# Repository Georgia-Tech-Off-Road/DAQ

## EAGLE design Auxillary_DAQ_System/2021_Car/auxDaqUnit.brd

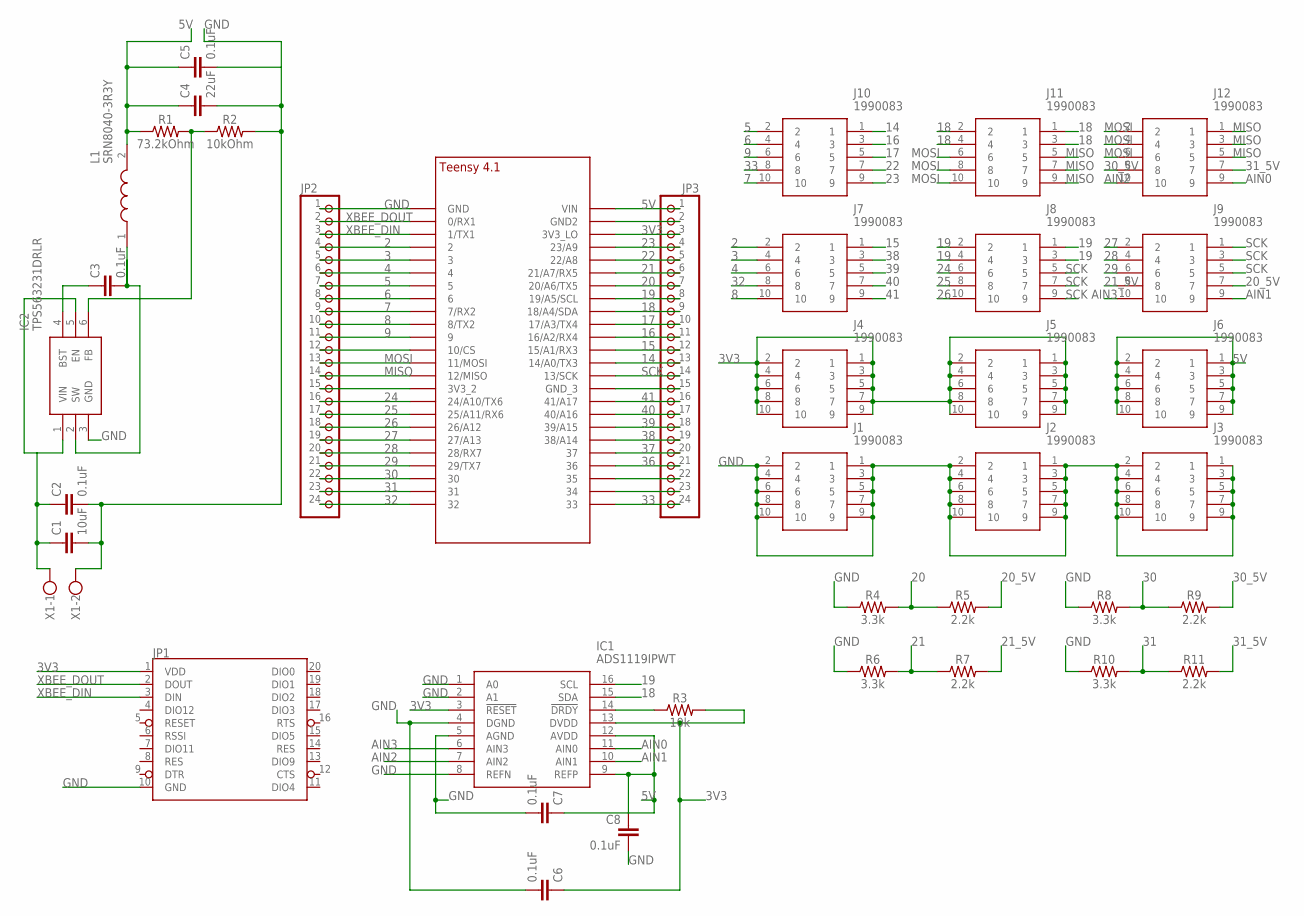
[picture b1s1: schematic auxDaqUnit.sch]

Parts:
C1: 10uF; 0603
C2, C3, C5, C6, C7, C8: 0.1uF; 0603
C4: 22uF; 0805
IC1: ADS1119IPWT; SOP65P640X120-16N
IC2: TPS563231DRLR; SOTFL50P160X60-6N
J1, J2, J3, J4, J5, J6, J7, J8, J9, J10, J11, J12: 1990083
JP1: XBEE
JP2, JP3: PINHD-1X24; 1X24
L1: SRN8040-3R3Y
R1: 73.2kOhm; 0603
R2: 10kOhm; 0603
R3: 10k; 0603
R4, R6, R8, R10: 3.3k; 0603
R5, R7, R9, R11: 2.2k; 0603
U$1: TEENSY_4.1_SIMPLE
X1: W237-102

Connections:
2: J7.2, JP2.4, U$1.2
3: J7.4, JP2.5, U$1.3/CANTX (3)
3V3: C6.1, IC1.3 (!RESET), IC1.13 (DVDD), J4.1, J4.2, J4.3, J4.4, J4.5, J4.6, J4.7, J4.8, J4.9, J4.10, J5.1, J5.2, J5.3, J5.4, J5.5, J5.6, J5.7, J5.8, J5.9, J5.10, JP1.1 (VDD), JP3.3, R3.2, U$1.3V3_LO
4: J7.6, JP2.6, U$1.4/CANRX (4)
5: J10.2, JP2.7, U$1.5
5V: C4.1, C5.1, C7.1, C8.1, IC1.9 (REFP), IC1.12 (AVDD), J6.1, J6.2, J6.3, J6.4, J6.5, J6.6, J6.7, J6.8, J6.9, J6.10, JP3.1, L1.2, R1.1, U$1.VIN
6: J10.4, JP2.8, U$1.6
7: J10.10, JP2.9, U$1.7 (7/RX2)
8: J7.10, JP2.10, U$1.8 (8/TX2)
9: J10.6, JP2.11, U$1.9/CS (9)
14: J10.1, JP3.13, U$1.14/A0 (14/A0/TX3)
15: J7.1, JP3.12, U$1.15/A1 (15/A1/RX3)
16: J10.3, JP3.11, U$1.16/A2 (16/A2/RX4)
17: J10.5, JP3.10, U$1.17/A3 (17/A3/TX4)
18: IC1.15 (SDA), J11.1, J11.2, J11.3, J11.4, JP3.9, U$1.18/A4/SDA
19: IC1.16 (SCL), J8.1, J8.2, J8.3, J8.4, JP3.8, U$1.19/A5/SCL
20: JP3.7, R4.2, R5.1, U$1.20/A6 (20/A6/TX5)
20_5V: J9.7, R5.2
21: JP3.6, R6.2, R7.1, U$1.21/A7 (21/A7/RX5)
21_5V: J9.8, R7.2
22: J10.7, JP3.5, U$1.22/A8
23: J10.9, JP3.4, U$1.23/A9
24: J8.6, JP2.16, U$1.24/A10 (24/A10/TX6)
25: J8.8, JP2.17, U$1.25/A11 (25/A11/RX6)
26: J8.10, JP2.18, U$1.26/A12
27: J9.2, JP2.19, U$1.27/A13
28: J9.4, JP2.20, U$1.28 (28/RX7)
29: J9.6, JP2.21, U$1.29 (29/TX7)
30: JP2.22, R8.2, R9.1, U$1.30
30_5V: J12.8, R9.2
31: JP2.23, R10.2, R11.1, U$1.31
31_5V: J12.7, R11.2
32: J7.8, JP2.24, U$1.32
33: J10.8, JP3.24, U$1.33
36: JP3.21, U$1.36
37: JP3.20, U$1.37
38: J7.3, JP3.19, U$1.38/A14
39: J7.5, JP3.18, U$1.39/A15
40: J7.7, JP3.17, U$1.40/A16
41: J7.9, JP3.16, U$1.41/A17
AIN0: IC1.11 (AIN0), J12.9
AIN1: IC1.10 (AIN1), J9.9
AIN2: IC1.7 (AIN2), J12.10
AIN3: IC1.6 (AIN3), J9.10
GND: C1.2, C2.2, C4.2, C5.2, C6.2, C7.2, C8.2, IC1.1 (A0), IC1.2 (A1), IC1.4 (DGND), IC1.5 (AGND), IC1.8 (REFN), IC2.3 (GND), J1.1, J1.2, J1.3, J1.4, J1.5, J1.6, J1.7, J1.8, J1.9, J1.10, J2.1, J2.2, J2.3, J2.4, J2.5, J2.6, J2.7, J2.8, J2.9, J2.10, J3.1, J3.2, J3.3, J3.4, J3.5, J3.6, J3.7, J3.8, J3.9, J3.10, JP1.10 (GND), JP2.1, R2.2, R4.1, R6.1, R8.1, R10.1, U$1.GND, X1.2
GNDBLOCK: JP3.2, U$1.GND2
MISO: J11.5, J11.7, J11.9, J12.1, J12.3, J12.5, JP2.14, U$1.12/MISO
MOSI: J11.6, J11.8, J11.10, J12.2, J12.4, J12.6, JP2.13, U$1.11/MOSI
unnamed: C3.1, IC2.4 (BST)
unnamed: C1.1, C2.1, IC2.1 (VIN), IC2.5 (EN), X1.1
unnamed: C3.2, IC2.2 (SW), L1.1
unnamed: IC1.14 (!DRDY), R3.1
unnamed: IC2.6 (FB), R1.2, R2.1
unnamed: JP2.12, U$1.10/CS
unnamed: JP2.15, U$1.3V3_2
unnamed: JP3.15, U$1.GND3 (GND_3)
unnamed: JP3.22, U$1.35
unnamed: JP3.23, U$1.34
SCK: J8.5, J8.7, J8.9, J9.1, J9.3, J9.5, JP3.14, U$1.13/SCK
XBEE_DIN: JP1.3 (DIN), JP2.3, U$1.1/TX (1/TX1)
XBEE_DOUT: JP1.2 (DOUT), JP2.2, U$1.0/RX (0/RX1)

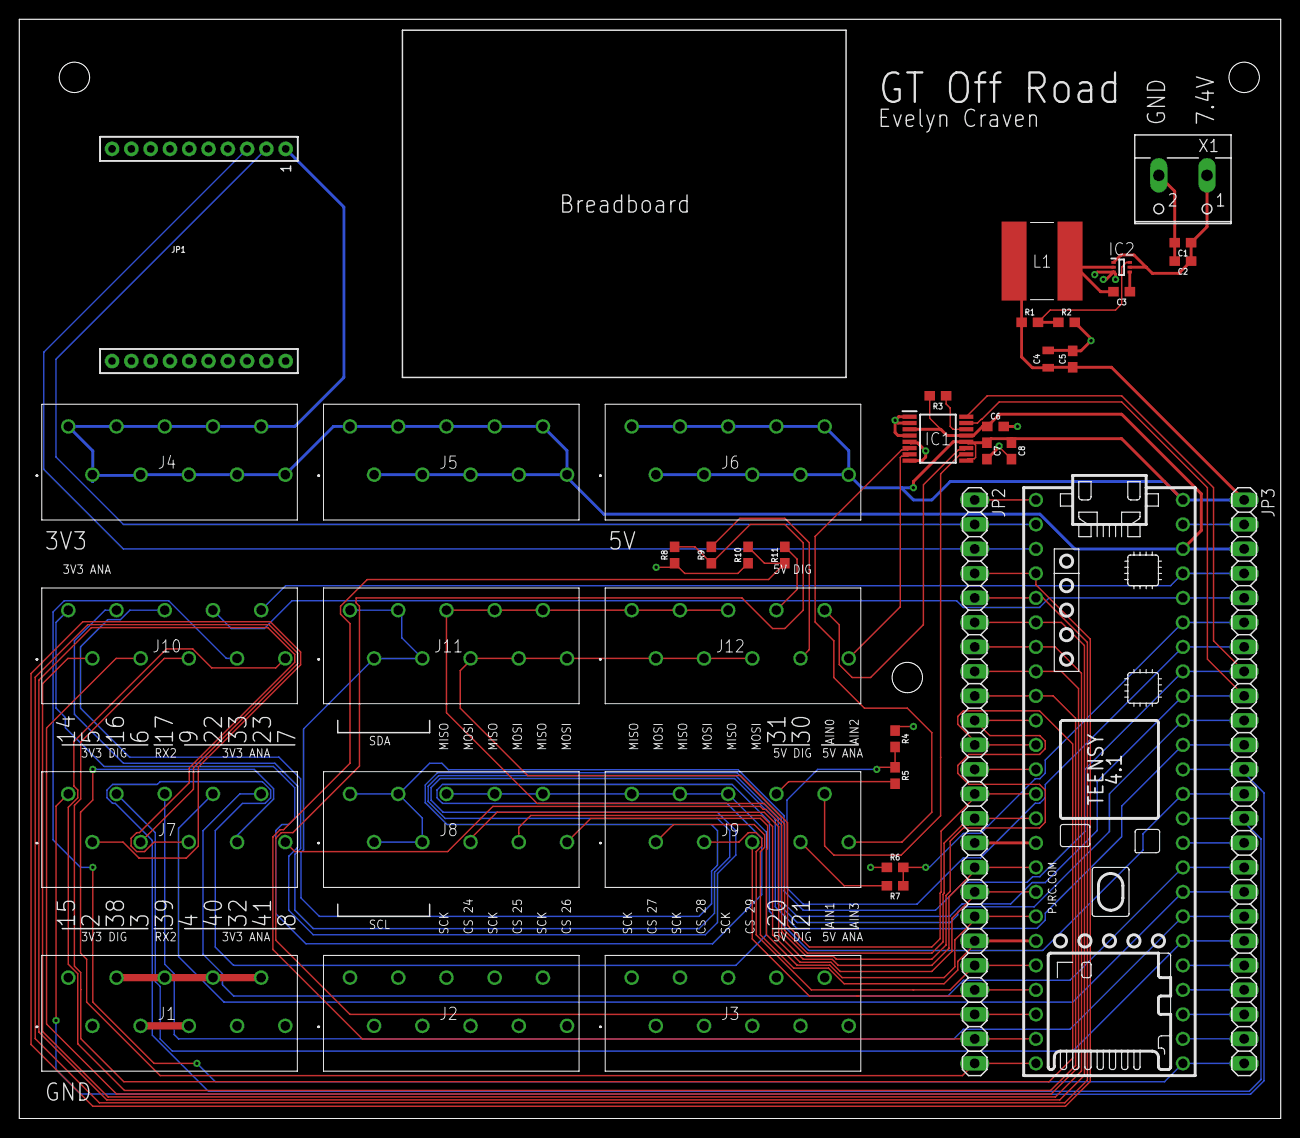
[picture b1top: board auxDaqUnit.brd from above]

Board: 2 copper layers, 130.8 x 114.0 mm, 39 parts (0 on the bottom side), 61 nets.

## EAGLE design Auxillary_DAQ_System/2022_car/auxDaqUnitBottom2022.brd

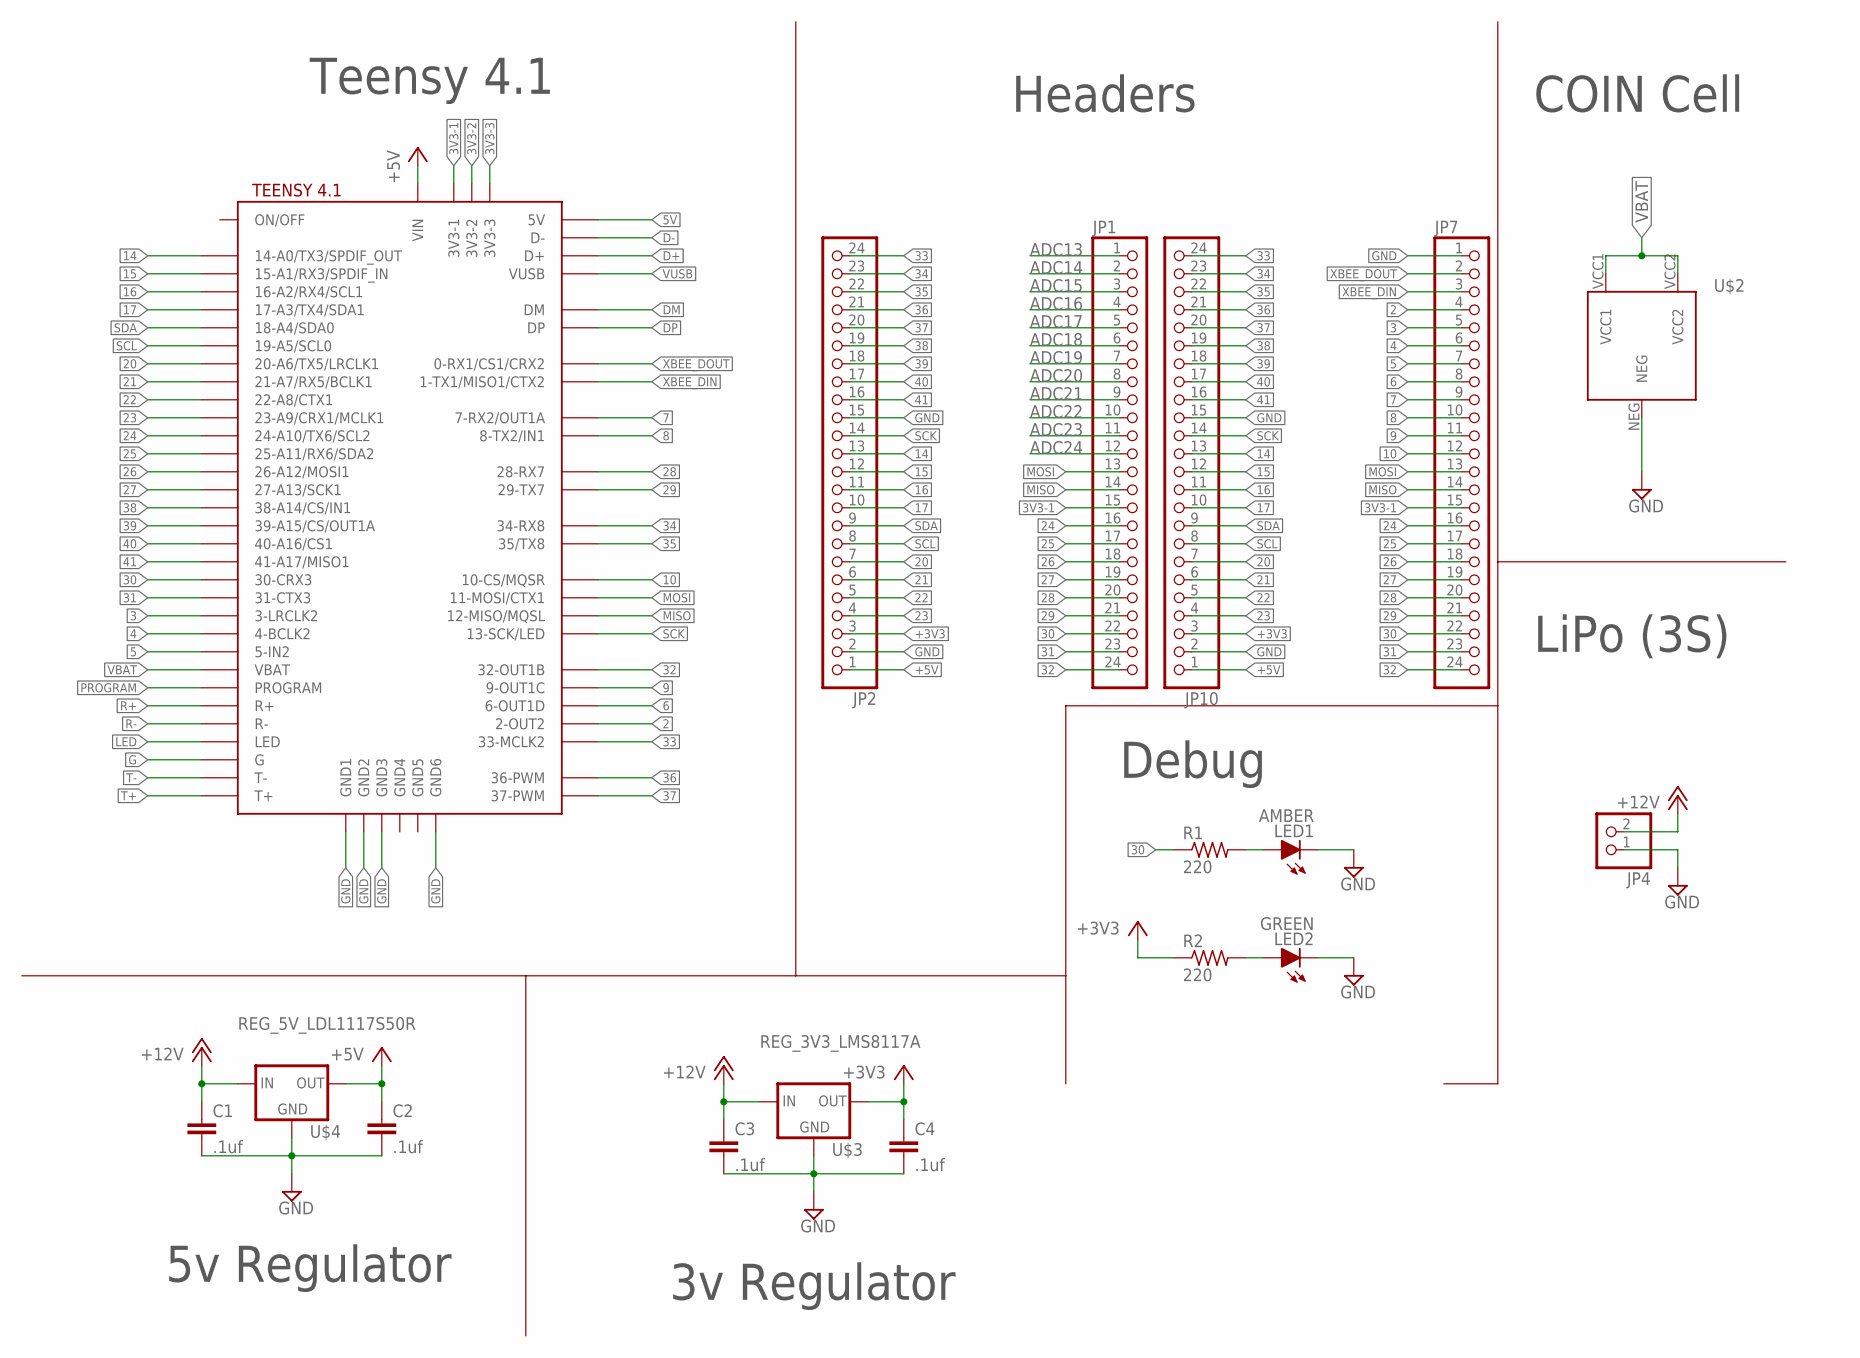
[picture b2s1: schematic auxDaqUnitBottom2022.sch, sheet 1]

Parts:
C1, C2, C3, C4: .1uf; C0603
JP1, JP2, JP7, JP10: PINHD-1X24; 1X24
JP4: PINHD-1X2; 1X02
LED1: AMBER; LED-603
LED2: GREEN; LED-603
R1, R2: 220; R0603
U$1: TEENSY41
U$2: KEYSTONE3035
U$3: REG_3V3_LMS8117A; SOT223
U$4: REG_5V_LDL1117S50R; SOT230P700X180-4N

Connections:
2: JP7.4, U$1.2-OUT2; also elsewhere on the board
3: JP7.5, U$1.3-LRCLK2; also elsewhere on the board
3V3-1: JP1.15, JP7.15, U$1.3V3-1
3V3-2: U$1.3V3-2
3V3-3: U$1.3V3-3
4: JP7.6, U$1.4-BCLK2; also elsewhere on the board
5: JP7.7, U$1.5-IN2; also elsewhere on the board
5V: U$1.+5V (5V)
6: JP7.8, U$1.6-OUT1D; also elsewhere on the board
7: JP7.9, U$1.7-RX2/OUT1A; also elsewhere on the board
8: JP7.10, U$1.8-TX2/IN2 (8-TX2/IN1); also elsewhere on the board
9: JP7.11, U$1.9-OUT1C; also elsewhere on the board
10: JP7.12, U$1.10-CS\MQSR (10-CS/MQSR); also elsewhere on the board
14: JP2.13, JP10.13, U$1.14-A0/TX3/SPDIF_OUT; also elsewhere on the board
15: JP2.12, JP10.12, U$1.15-A1/RX3/SPDIF_IN
16: JP2.11, JP10.11, U$1.16-A2/RX4/SCL1
17: JP2.10, JP10.10, U$1.17-A3/TX4/SDA1
20: JP2.7, JP10.7, U$1.20-A6/TX5/LRCLK1
21: JP2.6, JP10.6, U$1.21-A7/RX5/BCLK1
22: JP2.5, JP10.5, U$1.22-A8/CTX1
23: JP2.4, JP10.4, U$1.23-A9/CRX1/MCLK1
24: JP1.16, JP7.16, U$1.24-A10/TX6/SCL2
25: JP1.17, JP7.17, U$1.25-A11/RX6/SDA2
26: JP1.18, JP7.18, U$1.26-A12/MOSI1
27: JP1.19, JP7.19, U$1.27-A13/SCK1
28: JP1.20, JP7.20, U$1.28-RX7
29: JP1.21, JP7.21, U$1.29-TX7
30: JP1.22, JP7.22, R1.1, U$1.30-CRX3; also elsewhere on the board
31: JP1.23, JP7.23, U$1.31-CTX3; also elsewhere on the board
32: JP1.24, JP7.24, U$1.32-OUT1B; also elsewhere on the board
33: JP2.24, JP10.24, U$1.33-MCLK2; also elsewhere on the board
34: JP2.23, JP10.23, U$1.34-RX8; also elsewhere on the board
35: JP2.22, JP10.22, U$1.35-TX8 (35/TX8); also elsewhere on the board
36: JP2.21, JP10.21, U$1.36-PWM
37: JP2.20, JP10.20, U$1.37-PWM
38: JP2.19, JP10.19, U$1.38-A14/CS/IN1
39: JP2.18, JP10.18, U$1.39-A15/CS/OUT1A
40: JP2.17, JP10.17, U$1.40-A16/CS1
41: JP2.16, JP10.16, U$1.41-A17/MISO1
+3V3: C4.1, JP2.3, JP10.3, R2.1, U$3.2 (OUT), U$3.4 (OUT); also elsewhere on the board
+5V: C2.1, JP2.1, JP10.1, U$1.VIN, U$4.2 (OUT), U$4.4 (OUT); also elsewhere on the board
+12V: C1.1, C3.1, JP4.2, U$3.3 (IN), U$4.3 (IN)
ADC13: JP1.1; also elsewhere on the board
ADC14: JP1.2; also elsewhere on the board
ADC15: JP1.3; also elsewhere on the board
ADC16: JP1.4; also elsewhere on the board
ADC17: JP1.5; also elsewhere on the board
ADC18: JP1.6; also elsewhere on the board
ADC19: JP1.7; also elsewhere on the board
ADC20: JP1.8; also elsewhere on the board
ADC21: JP1.9; also elsewhere on the board
ADC22: JP1.10; also elsewhere on the board
ADC23: JP1.11; also elsewhere on the board
ADC24: JP1.12; also elsewhere on the board
D+: U$1.D+
D-: U$1.D-
DM: U$1.DM
DP: U$1.DP
G: U$1.G
GND: C1.2, C2.2, C3.2, C4.2, JP2.2, JP2.15, JP4.1, JP7.1, JP10.2, JP10.15, LED1.C, LED2.C, U$1.GND1, U$1.GND2, U$1.GND3, U$1.GND6, U$2.NEG, U$3.1 (GND), U$4.1 (GND); also elsewhere on the board
LED: U$1.LED
MISO: JP1.14, JP7.14, U$1.12-MISO/MQSL; also elsewhere on the board
MOSI: JP1.13, JP7.13, U$1.11-MOSI/CTX1; also elsewhere on the board
unnamed: LED1.A, R1.2
unnamed: LED2.A, R2.2
PROGRAM: U$1.PROGRAM
R+: U$1.R+
R-: U$1.R-
SCK: JP2.14, JP10.14, U$1.13-SCK/LED; also elsewhere on the board
SCL: JP2.8, JP10.8, U$1.19-A5/SCL0; also elsewhere on the board
SDA: JP2.9, JP10.9, U$1.18-A4/SDA0; also elsewhere on the board
T+: U$1.T+
T-: U$1.T-
VBAT: U$1.VBAT, U$2.VCC1, U$2.VCC2
VUSB: U$1.VUSB
XBEE_DIN: JP7.3, U$1.1-TX1/MISO1/CTX2; also elsewhere on the board
XBEE_DOUT: JP7.2, U$1.0-RX1/CS1/CRX2; also elsewhere on the board

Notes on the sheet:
5v Regulator
3v Regulator
Teensy 4.1
Headers
COIN Cell
LiPo (3S)
Debug

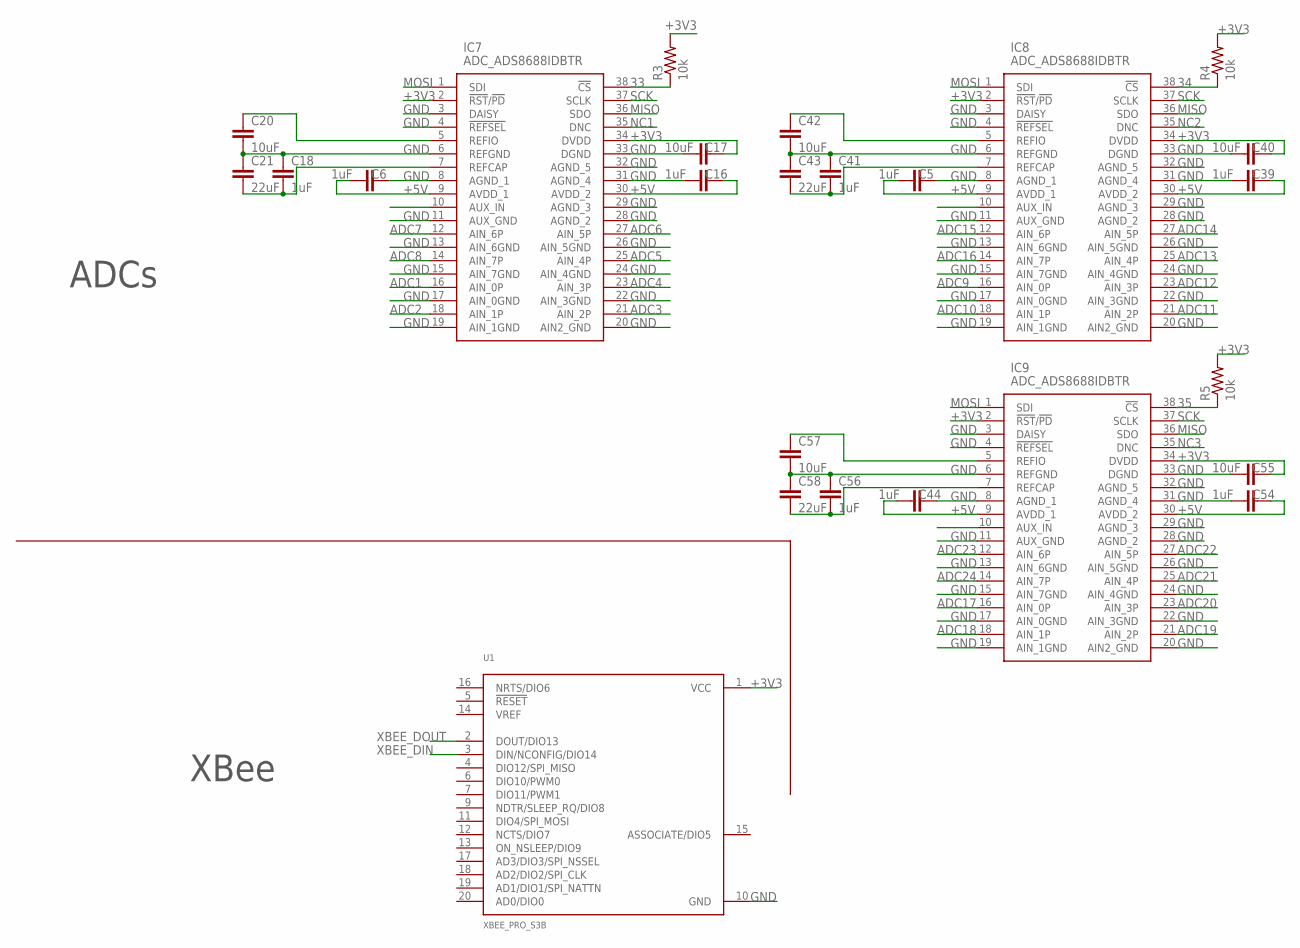
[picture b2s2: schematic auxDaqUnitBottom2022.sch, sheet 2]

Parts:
C5, C6, C16, C18, C39, C41, C44, C54, C56: 1uF; C0603
C17, C40, C55: 10uF; C0603
C20, C42, C57: 10uF; C0805
C21, C43, C58: 22uF; C1210
IC7, IC8, IC9: ADC_ADS8688IDBTR; SOP50P640X120-38N
R3, R4, R5: 10k; R0603
U1: XBEE_PRO_S3B

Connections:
33: IC7.38 (!CS), R3.1; also elsewhere on the board
34: IC8.38 (!CS), R4.1; also elsewhere on the board
35: IC9.38 (!CS), R5.1; also elsewhere on the board
+3V3: C17.1, C40.1, C55.1, IC7.2 (!RST!/!PD), IC7.34 (DVDD), IC8.2 (!RST!/!PD), IC8.34 (DVDD), IC9.2 (!RST!/!PD), IC9.34 (DVDD), R3.2, R4.2, R5.2, U1.1 (VCC); also elsewhere on the board
+5V: C5.2, C6.2, C16.1, C39.1, C44.2, C54.1, IC7.9 (AVDD_1), IC7.30 (AVDD_2), IC8.9 (AVDD_1), IC8.30 (AVDD_2), IC9.9 (AVDD_1), IC9.30 (AVDD_2); also elsewhere on the board
ADC1: IC7.16 (AIN_0P); also elsewhere on the board
ADC2: IC7.18 (AIN_1P); also elsewhere on the board
ADC3: IC7.21 (AIN_2P); also elsewhere on the board
ADC4: IC7.23 (AIN_3P); also elsewhere on the board
ADC5: IC7.25 (AIN_4P); also elsewhere on the board
ADC6: IC7.27 (AIN_5P); also elsewhere on the board
ADC7: IC7.12 (AIN_6P); also elsewhere on the board
ADC8: IC7.14 (AIN_7P); also elsewhere on the board
ADC9: IC8.16 (AIN_0P); also elsewhere on the board
ADC10: IC8.18 (AIN_1P); also elsewhere on the board
ADC11: IC8.21 (AIN_2P); also elsewhere on the board
ADC12: IC8.23 (AIN_3P); also elsewhere on the board
ADC13: IC8.25 (AIN_4P); also elsewhere on the board
ADC14: IC8.27 (AIN_5P); also elsewhere on the board
ADC15: IC8.12 (AIN_6P); also elsewhere on the board
ADC16: IC8.14 (AIN_7P); also elsewhere on the board
ADC17: IC9.16 (AIN_0P); also elsewhere on the board
ADC18: IC9.18 (AIN_1P); also elsewhere on the board
ADC19: IC9.21 (AIN_2P); also elsewhere on the board
ADC20: IC9.23 (AIN_3P); also elsewhere on the board
ADC21: IC9.25 (AIN_4P); also elsewhere on the board
ADC22: IC9.27 (AIN_5P); also elsewhere on the board
ADC23: IC9.12 (AIN_6P); also elsewhere on the board
ADC24: IC9.14 (AIN_7P); also elsewhere on the board
GND: C5.1, C6.1, C16.2, C17.2, C18.1, C20.2, C21.1, C39.2, C40.2, C41.1, C42.2, C43.1, C44.1, C54.2, C55.2, C56.1, C57.2, C58.1, IC7.3 (DAISY), IC7.4 (!REFSEL), IC7.6 (REFGND), IC7.8 (AGND_1), IC7.11 (AUX_GND), IC7.13 (AIN_6GND), IC7.15 (AIN_7GND), IC7.17 (AIN_0GND), IC7.19 (AIN_1GND), IC7.20 (AIN2_GND), IC7.22 (AIN_3GND), IC7.24 (AIN_4GND), IC7.26 (AIN_5GND), IC7.28 (AGND_2), IC7.29 (AGND_3), IC7.31 (AGND_4), IC7.32 (AGND_5), IC7.33 (DGND), IC8.3 (DAISY), IC8.4 (!REFSEL), IC8.6 (REFGND), IC8.8 (AGND_1), IC8.11 (AUX_GND), IC8.13 (AIN_6GND), IC8.15 (AIN_7GND), IC8.17 (AIN_0GND), IC8.19 (AIN_1GND), IC8.20 (AIN2_GND), IC8.22 (AIN_3GND), IC8.24 (AIN_4GND), IC8.26 (AIN_5GND), IC8.28 (AGND_2), IC8.29 (AGND_3), IC8.31 (AGND_4), IC8.32 (AGND_5), IC8.33 (DGND), IC9.3 (DAISY), IC9.4 (!REFSEL), IC9.6 (REFGND), IC9.8 (AGND_1), IC9.11 (AUX_GND), IC9.13 (AIN_6GND), IC9.15 (AIN_7GND), IC9.17 (AIN_0GND), IC9.19 (AIN_1GND), IC9.20 (AIN2_GND), IC9.22 (AIN_3GND), IC9.24 (AIN_4GND), IC9.26 (AIN_5GND), IC9.28 (AGND_2), IC9.29 (AGND_3), IC9.31 (AGND_4), IC9.32 (AGND_5), IC9.33 (DGND), U1.10 (GND); also elsewhere on the board
MISO: IC7.36 (SDO), IC8.36 (SDO), IC9.36 (SDO); also elsewhere on the board
MOSI: IC7.1 (SDI), IC8.1 (SDI), IC9.1 (SDI); also elsewhere on the board
unnamed: C20.1, IC7.5 (REFIO)
unnamed: C41.2, C43.2, IC8.7 (REFCAP)
unnamed: C18.2, C21.2, IC7.7 (REFCAP)
unnamed: C42.1, IC8.5 (REFIO)
unnamed: C56.2, C58.2, IC9.7 (REFCAP)
unnamed: C57.1, IC9.5 (REFIO)
NC1: IC7.35 (DNC)
NC2: IC8.35 (DNC)
NC3: IC9.35 (DNC)
SCK: IC7.37 (SCLK), IC8.37 (SCLK), IC9.37 (SCLK); also elsewhere on the board
XBEE_DIN: U1.3 (DIN/NCONFIG/DIO14); also elsewhere on the board
XBEE_DOUT: U1.2 (DOUT/DIO13); also elsewhere on the board

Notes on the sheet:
XBee
ADCs

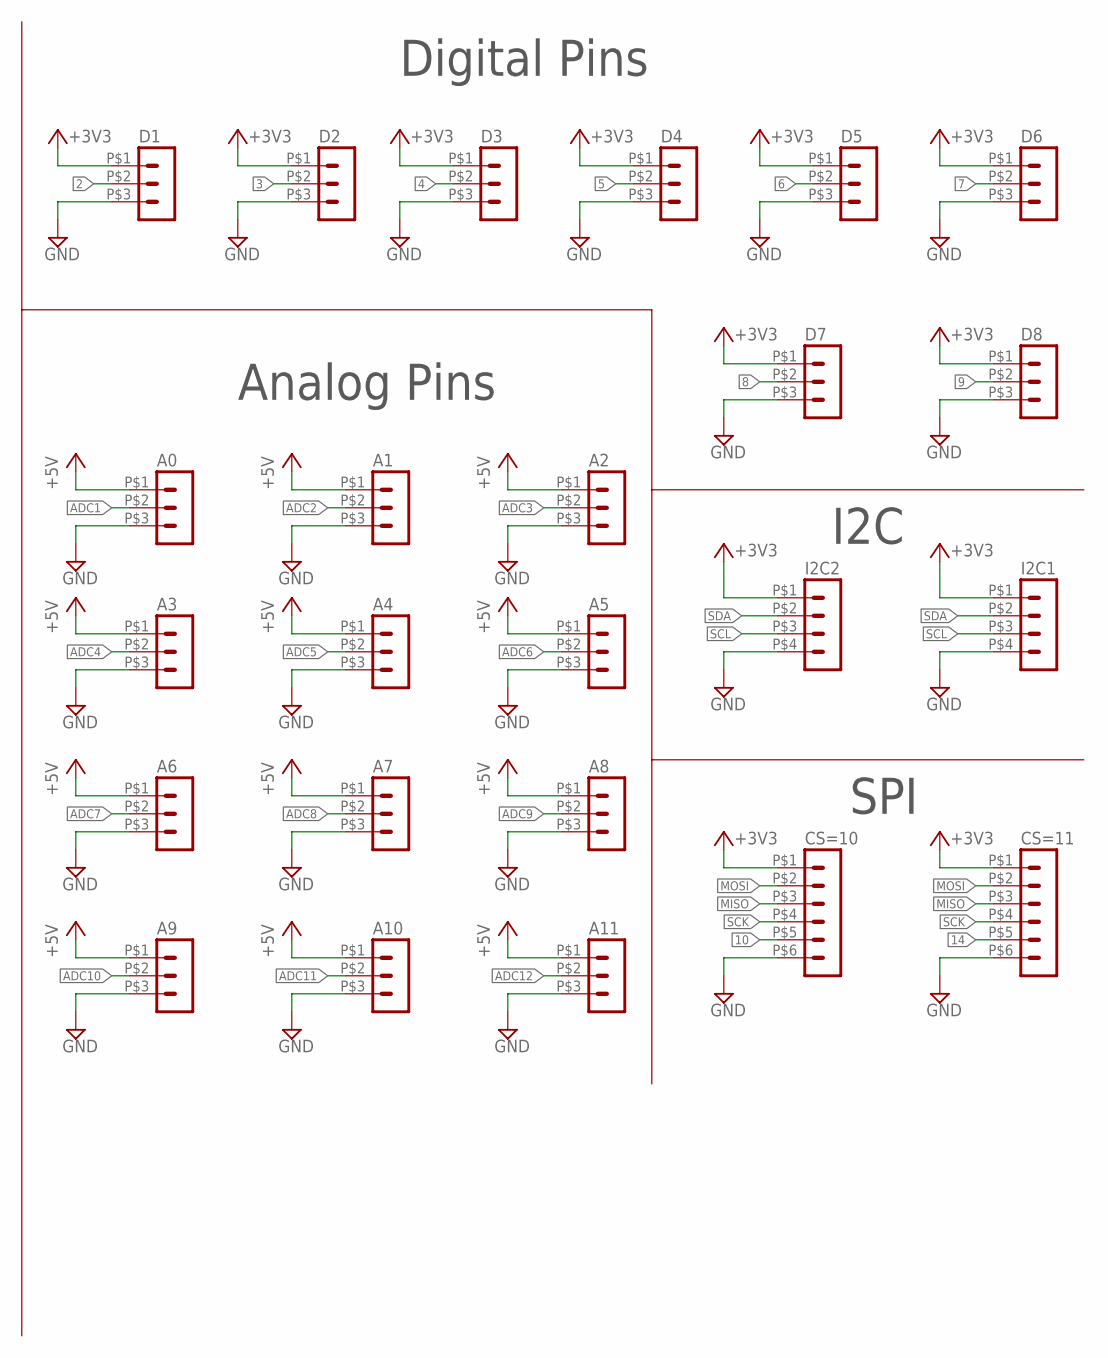
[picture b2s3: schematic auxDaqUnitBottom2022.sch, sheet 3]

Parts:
A0, A1, A2, A3, A4, A5, A6, A7, A8, A9, A10, A11: HEADER_POS3_43650-0300; 43650-0300
CS=10, CS=11: HEADER_POS6_43045-0600; 43045-0600
D1, D2, D3, D4, D5, D6, D7, D8: HEADER_POS3_43650-0300; 43650-0300
I2C1, I2C2: HEADER_POS4_43045-0401; 43045-0400

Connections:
2: D1.P$2 (2); also elsewhere on the board
3: D2.P$2 (2); also elsewhere on the board
4: D3.P$2 (2); also elsewhere on the board
5: D4.P$2 (2); also elsewhere on the board
6: D5.P$2 (2); also elsewhere on the board
7: D6.P$2 (2); also elsewhere on the board
8: D7.P$2 (2); also elsewhere on the board
9: D8.P$2 (2); also elsewhere on the board
10: CS=10.P$5 (5); also elsewhere on the board
14: CS=11.P$5 (5); also elsewhere on the board
+3V3: CS=10.P$1 (1), CS=11.P$1 (1), D1.P$1 (1), D2.P$1 (1), D3.P$1 (1), D4.P$1 (1), D5.P$1 (1), D6.P$1 (1), D7.P$1 (1), D8.P$1 (1), I2C1.P$1 (1), I2C2.P$1 (1); also elsewhere on the board
+5V: A0.P$1 (1), A1.P$1 (1), A2.P$1 (1), A3.P$1 (1), A4.P$1 (1), A5.P$1 (1), A6.P$1 (1), A7.P$1 (1), A8.P$1 (1), A9.P$1 (1), A10.P$1 (1), A11.P$1 (1); also elsewhere on the board
ADC1: A0.P$2 (2); also elsewhere on the board
ADC2: A1.P$2 (2); also elsewhere on the board
ADC3: A2.P$2 (2); also elsewhere on the board
ADC4: A3.P$2 (2); also elsewhere on the board
ADC5: A4.P$2 (2); also elsewhere on the board
ADC6: A5.P$2 (2); also elsewhere on the board
ADC7: A6.P$2 (2); also elsewhere on the board
ADC8: A7.P$2 (2); also elsewhere on the board
ADC9: A8.P$2 (2); also elsewhere on the board
ADC10: A9.P$2 (2); also elsewhere on the board
ADC11: A10.P$2 (2); also elsewhere on the board
ADC12: A11.P$2 (2); also elsewhere on the board
GND: A0.P$3 (3), A1.P$3 (3), A2.P$3 (3), A3.P$3 (3), A4.P$3 (3), A5.P$3 (3), A6.P$3 (3), A7.P$3 (3), A8.P$3 (3), A9.P$3 (3), A10.P$3 (3), A11.P$3 (3), CS=10.P$6 (6), CS=11.P$6 (6), D1.P$3 (3), D2.P$3 (3), D3.P$3 (3), D4.P$3 (3), D5.P$3 (3), D6.P$3 (3), D7.P$3 (3), D8.P$3 (3), I2C1.P$4 (4), I2C2.P$4 (4); also elsewhere on the board
MISO: CS=10.P$3 (3), CS=11.P$3 (3); also elsewhere on the board
MOSI: CS=10.P$2 (2), CS=11.P$2 (2); also elsewhere on the board
SCK: CS=10.P$4 (4), CS=11.P$4 (4); also elsewhere on the board
SCL: I2C1.P$3 (3), I2C2.P$3 (3); also elsewhere on the board
SDA: I2C1.P$2 (2), I2C2.P$2 (2); also elsewhere on the board

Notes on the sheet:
SPI
I2C
Digital Pins
Analog Pins

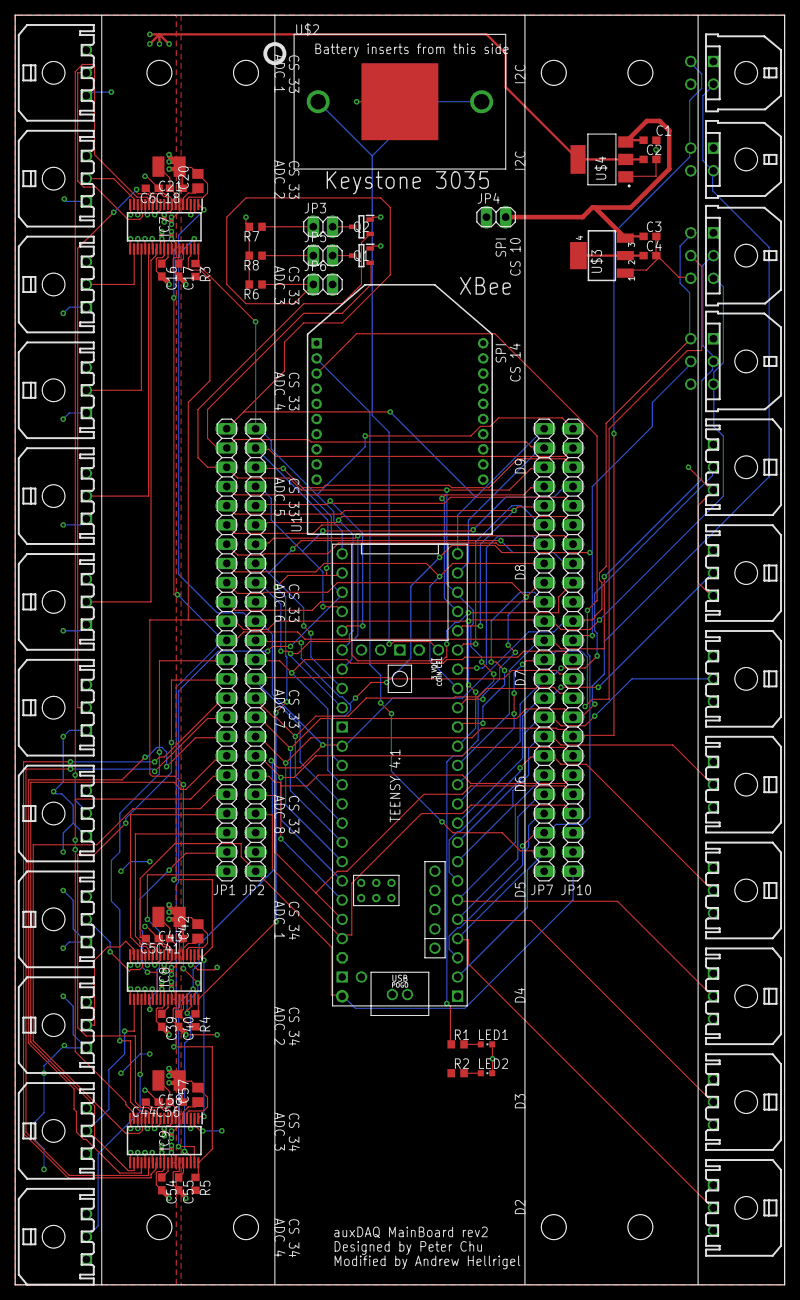
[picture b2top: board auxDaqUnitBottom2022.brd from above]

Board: 2 copper layers, 101.6 x 167.6 mm, 74 parts (0 on the bottom side), 85 nets.

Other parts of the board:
JP3, JP5, JP6: 1X02
Q1, Q2: MOSFET_N-TYPE_RK7002BMT116; BSS64AHZGT116
R6: 10k; R0603
R7, R8: R0603

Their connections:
3V3: R6.2, R7.2, R8.2
30: Q2.2; also elsewhere on the board
31: Q1.2; also elsewhere on the board
32: JP6.1, R6.1; also elsewhere on the board
GND: JP6.2, Q1.1, Q2.1; also elsewhere on the board
LED1_GND: JP3.2, Q2.3
LED2_GND: JP5.2, Q1.3
unnamed: JP3.1, R7.1
unnamed: JP5.1, R8.1

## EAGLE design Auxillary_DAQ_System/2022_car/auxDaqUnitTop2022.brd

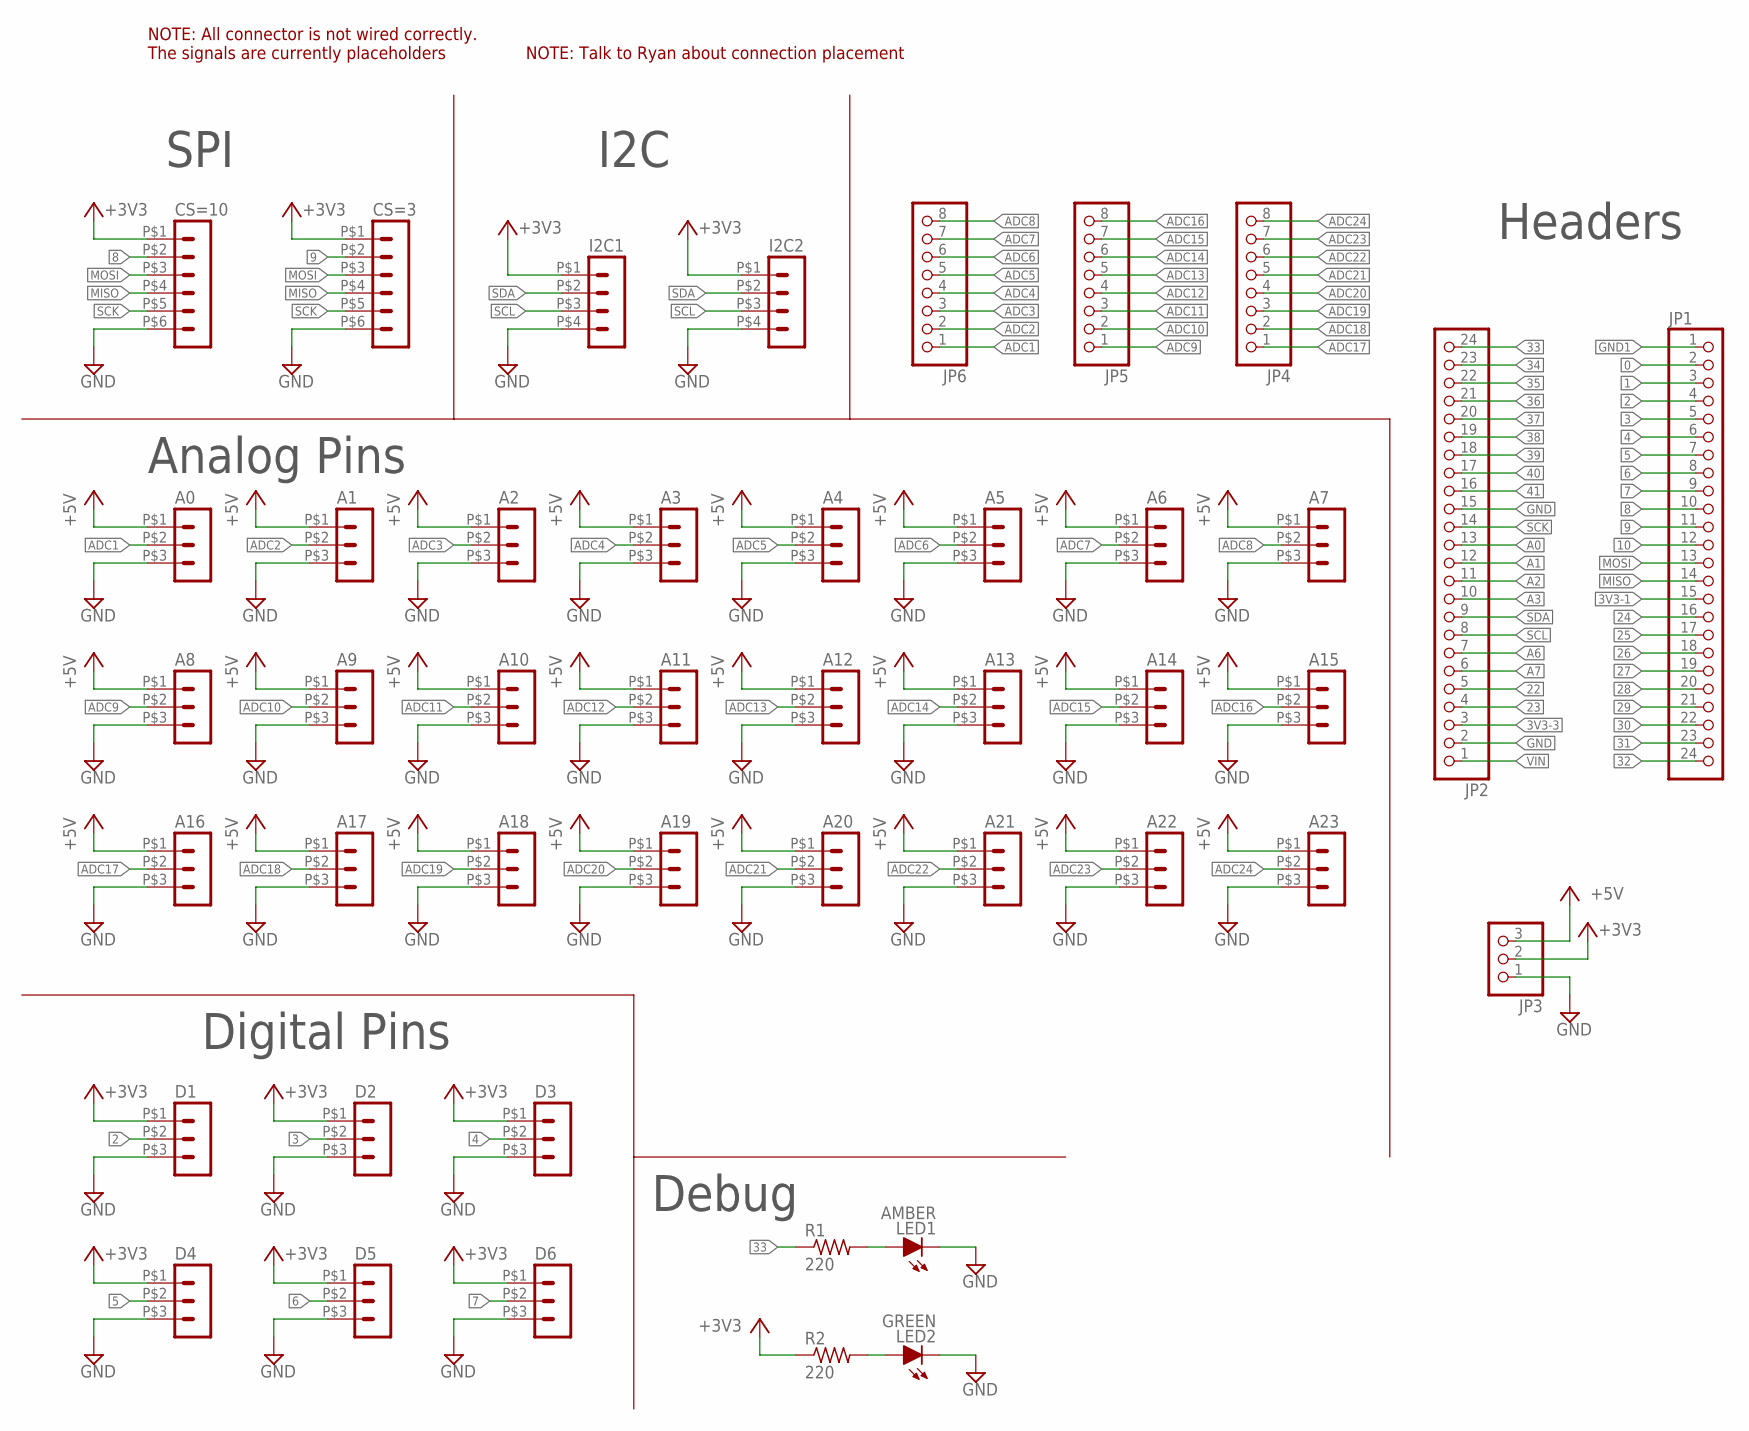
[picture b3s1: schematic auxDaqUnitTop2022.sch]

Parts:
A0, A1, A2, A3, A4, A5, A6, A7, A8, A9, A10, A11, A12, A13, A14, A15, A16, A17, A18, A19, A20, A21, A22, A23: HEADER_POS3_43650-0300; 43650-0300
CS=3, CS=10: HEADER_POS6_43045-0600; 43045-0600
D1, D2, D3, D4, D5, D6: HEADER_POS3_43650-0300; 43650-0300
I2C1, I2C2: HEADER_POS4_43045-0401; 43045-0400
JP1, JP2: PINHD-1X24; 1X24
JP3: PINHD-1X3; 1X03
JP4, JP5, JP6: PINHD-1X8; 1X08
LED1: AMBER; LED-603
LED2: GREEN; LED-603
R1, R2: 220; R0603

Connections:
0: JP1.2
1: JP1.3
2: D1.P$2 (2), JP1.4
3: D2.P$2 (2), JP1.5
3V3-1: JP1.15
3V3-3: JP2.3
4: D3.P$2 (2), JP1.6
5: D4.P$2 (2), JP1.7
6: D5.P$2 (2), JP1.8
7: D6.P$2 (2), JP1.9
8: CS=10.P$2 (2), JP1.10
9: CS=3.P$2 (2), JP1.11
10: JP1.12
22: JP2.5
23: JP2.4
24: JP1.16
25: JP1.17
26: JP1.18
27: JP1.19
28: JP1.20
29: JP1.21
30: JP1.22
31: JP1.23
32: JP1.24
33: JP2.24, R1.1
34: JP2.23
35: JP2.22
36: JP2.21
37: JP2.20
38: JP2.19
39: JP2.18
40: JP2.17
41: JP2.16
+3V3: CS=3.P$1 (1), CS=10.P$1 (1), D1.P$1 (1), D2.P$1 (1), D3.P$1 (1), D4.P$1 (1), D5.P$1 (1), D6.P$1 (1), I2C1.P$1 (1), I2C2.P$1 (1), JP3.2, R2.1
+5V: A0.P$1 (1), A1.P$1 (1), A2.P$1 (1), A3.P$1 (1), A4.P$1 (1), A5.P$1 (1), A6.P$1 (1), A7.P$1 (1), A8.P$1 (1), A9.P$1 (1), A10.P$1 (1), A11.P$1 (1), A12.P$1 (1), A13.P$1 (1), A14.P$1 (1), A15.P$1 (1), A16.P$1 (1), A17.P$1 (1), A18.P$1 (1), A19.P$1 (1), A20.P$1 (1), A21.P$1 (1), A22.P$1 (1), A23.P$1 (1), JP3.3
A0: JP2.13
A1: JP2.12
A2: JP2.11
A3: JP2.10
A6: JP2.7
A7: JP2.6
ADC1: A0.P$2 (2), JP6.1
ADC2: A1.P$2 (2), JP6.2
ADC3: A2.P$2 (2), JP6.3
ADC4: A3.P$2 (2), JP6.4
ADC5: A4.P$2 (2), JP6.5
ADC6: A5.P$2 (2), JP6.6
ADC7: A6.P$2 (2), JP6.7
ADC8: A7.P$2 (2), JP6.8
ADC9: A8.P$2 (2), JP5.1
ADC10: A9.P$2 (2), JP5.2
ADC11: A10.P$2 (2), JP5.3
ADC12: A11.P$2 (2), JP5.4
ADC13: A12.P$2 (2), JP5.5
ADC14: A13.P$2 (2), JP5.6
ADC15: A14.P$2 (2), JP5.7
ADC16: A15.P$2 (2), JP5.8
ADC17: A16.P$2 (2), JP4.1
ADC18: A17.P$2 (2), JP4.2
ADC19: A18.P$2 (2), JP4.3
ADC20: A19.P$2 (2), JP4.4
ADC21: A20.P$2 (2), JP4.5
ADC22: A21.P$2 (2), JP4.6
ADC23: A22.P$2 (2), JP4.7
ADC24: A23.P$2 (2), JP4.8
GND: A0.P$3 (3), A1.P$3 (3), A2.P$3 (3), A3.P$3 (3), A4.P$3 (3), A5.P$3 (3), A6.P$3 (3), A7.P$3 (3), A8.P$3 (3), A9.P$3 (3), A10.P$3 (3), A11.P$3 (3), A12.P$3 (3), A13.P$3 (3), A14.P$3 (3), A15.P$3 (3), A16.P$3 (3), A17.P$3 (3), A18.P$3 (3), A19.P$3 (3), A20.P$3 (3), A21.P$3 (3), A22.P$3 (3), A23.P$3 (3), CS=3.P$6 (6), CS=10.P$6 (6), D1.P$3 (3), D2.P$3 (3), D3.P$3 (3), D4.P$3 (3), D5.P$3 (3), D6.P$3 (3), I2C1.P$4 (4), I2C2.P$4 (4), JP2.2, JP2.15, JP3.1, LED1.C, LED2.C
GND1: JP1.1
MISO: CS=3.P$4 (4), CS=10.P$4 (4), JP1.14
MOSI: CS=3.P$3 (3), CS=10.P$3 (3), JP1.13
unnamed: LED1.A, R1.2
unnamed: LED2.A, R2.2
SCK: CS=3.P$5 (5), CS=10.P$5 (5), JP2.14
SCL: I2C1.P$3 (3), I2C2.P$3 (3), JP2.8
SDA: I2C1.P$2 (2), I2C2.P$2 (2), JP2.9
VIN: JP2.1

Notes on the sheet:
Headers
NOTE: All connector is not wired correctly. The signals are currently placeholders
SPI
I2C
Digital Pins
Analog Pins
Debug
NOTE: Talk to Ryan about connection placement

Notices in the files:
parts and their libraries:
SparkFun-RF: Licensing: Creative Commons ShareAlike 4.0 International - https://creativecommons.org/licenses/by-sa/4.0
diy-modules: Released under the Creative Commons Attribution 4.0 International License: http://creativecommons.org/licenses/by/4.0
